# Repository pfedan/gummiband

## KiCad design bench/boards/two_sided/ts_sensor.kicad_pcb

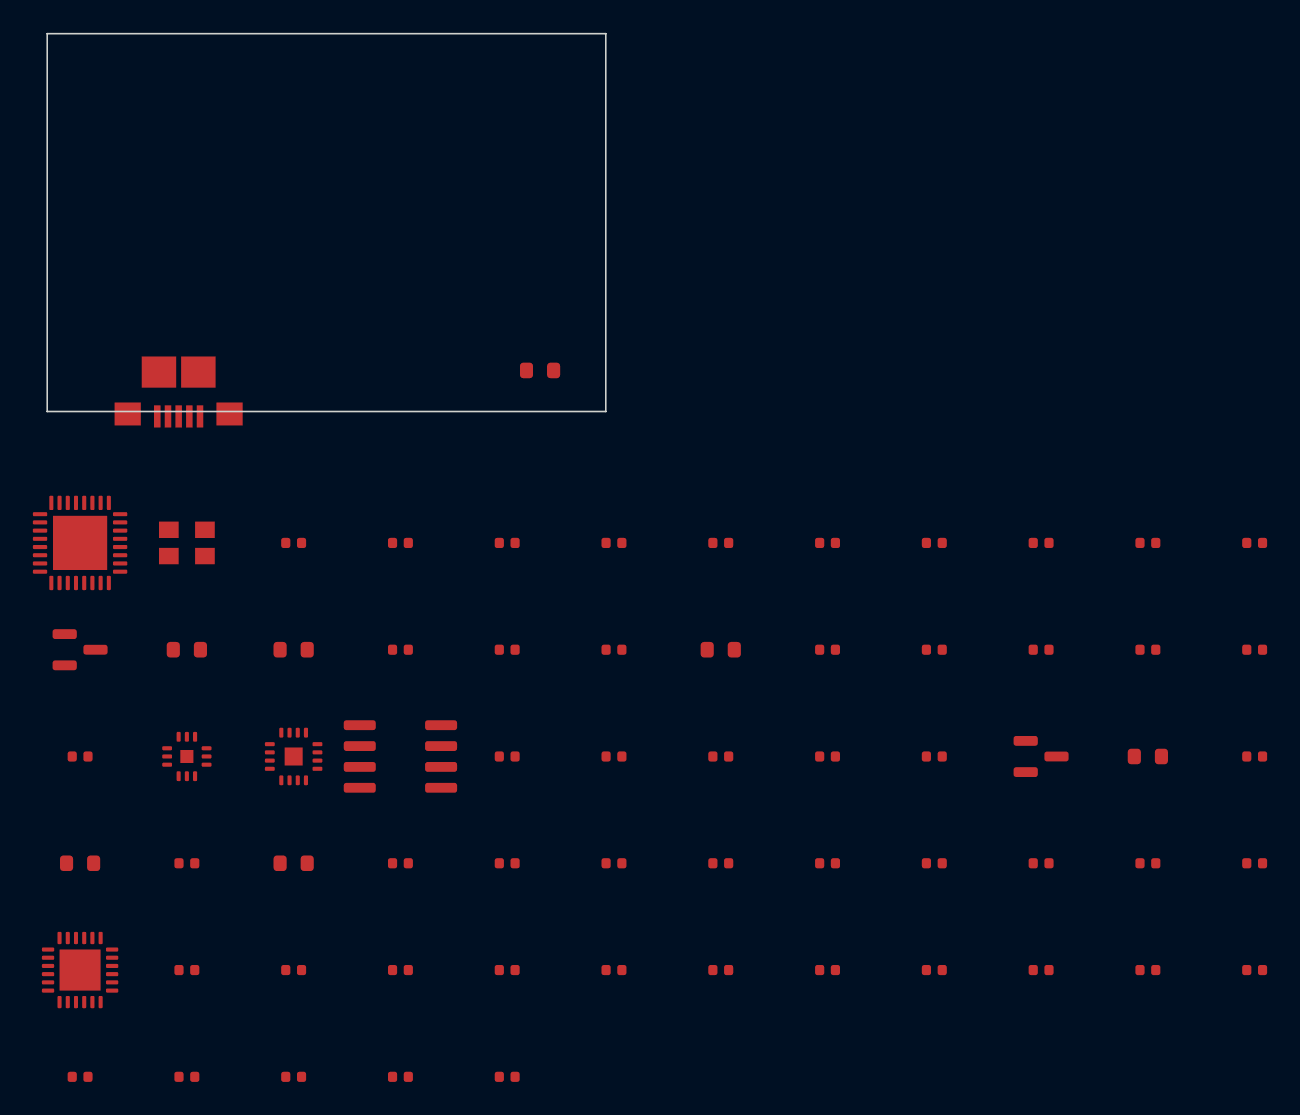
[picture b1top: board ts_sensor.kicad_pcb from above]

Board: 2 copper layers, 34.0 x 23.0 mm, 68 parts (1 on the bottom side), 59 nets, no tracks yet.

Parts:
BT1: CR2032; BatteryHolder_CR2032
C1, C2: 12p; C_0402
C11, C13: 2n2; C_0402
C20, C21, C22, C23: 1p; C_0402
C30, C31, C32, C60, C61, C62, C63, C64, C65, C66, C67, C68, C69: 1u; C_0402
C33: 10u; C_0603
C34, C35, C36, C37, C38, C39, C50, C51, C52: 100n; C_0402
D1, D2: BAT54; D_0603
D10, D11, D12: LED; D_0603
J1: USB; USB_Micro-B_SMD
L10, L12: 2n2; L_0402
R1, R2: 22; R_0402
R10, R11, R12: 1k; R_0402
R20, R21, R22, R23, R24, R25: 10k; R_0402
R30, R31: 1M; R_0402
R40, R41, R42, R43, R44, R45: 47k; R_0402
SW1: BTN; R_0603
U1: Radio; QFN-32
U2: LDO; SOT-23
U3: BME; QFN-12
U4: ACC; QFN-16
U5: Flash; SOIC-8
U6: ESD; SOT-23
U7: EPD; QFN-24
Y1: 32M; Crystal_3225

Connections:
+3V3: C32.1, C33.1, C34.1, C35.1, C36.1, C37.1, C38.1, C39.1, C50.1, C51.1, C52.1, R20.1, R21.1, R22.1, R23.1, R24.1, R25.1, R40.1, R41.1, R42.1, R43.1, R44.1, R45.1, U1.1, U1.9, U1.25, U2.3, U3.1, U4.1, U5.8, U7.1
BTN: SW1.1, U1.29
BUS0: U1.2, U3.2
BUS1: U1.3, U3.3
BUS2: U1.4, U4.2
BUS3: U1.7, U4.3
BUS4: U1.8, U4.4
BUS5: U1.10, U4.5
BUS6: U1.11, U5.1
BUS7: U1.12, U5.2
BUS8: U1.13, U5.3
BUS9: U1.14, U5.5
CP0: C60.1, U7.2
CP1: C61.1, U7.3
CP2: C62.1, U7.4
CP3: C63.1, U7.5
CP4: C64.1, U7.6
CP5: C65.1, U7.7
CP6: C66.1, U7.8
CP7: C67.1, U7.9
CP8: C68.1, U7.10
CP9: C69.1, U7.11
D0: R1.2, U1.15
D1: R2.2, U1.16
DP0: R40.2, U7.15
DP1: R41.2, U7.16
DP2: R42.2, U7.17
DP3: R43.2, U7.18
DP4: R44.2, U7.19
DP5: R45.2, U7.20
GND: BT1.3, C1.2, C2.2, C20.2, C21.2, C22.2, C23.2, C30.2, C31.2, C32.2, C33.2, C34.2, C35.2, C36.2, C37.2, C38.2, C39.2, C50.2, C51.2, C52.2, C60.2, C61.2, C62.2, C63.2, C64.2, C65.2, C66.2, C67.2, C68.2, C69.2, D10.2, D11.2, D12.2, J1.5, J1.S1, J1.S2, J1.S3, J1.S4, R31.2, SW1.2, U1.33, U2.1, U3.13, U4.17, U5.4, U6.3, U7.25, Y1.2, Y1.4
LED0: D10.1, R10.1
LED1: D11.1, R11.1
LED2: D12.1, R12.1
LEDC0: R10.2, U1.18
LEDC1: R11.2, U1.19
LEDC2: R12.2, U1.20
PU0: R20.2, U1.21
PU1: R21.2, U1.22
PU2: R22.2, U1.23
PU3: R23.2, U1.24
PU4: R24.2, U1.26
PU5: R25.2, U1.27
RF0: L10.1, U1.17
RF1: C11.1, C20.1, L10.2
RF2: C11.2, C21.1, L12.1
RF3: C13.1, C22.1, L12.2
RF4: C13.2, C23.1
SPI0: U1.30, U7.12
SPI1: U1.31, U7.13
SPI2: U1.32, U7.14
USB5: J1.2, R1.1, U6.1
USB6: J1.3, R2.1, U6.2
VBAT: BT1.1, BT1.2, D2.1, R30.1
VBUS: D1.1, J1.1
VDIV: R30.2, R31.1, U1.28
VIN: C30.1, C31.1, D1.2, D2.2, U2.2
XI: C1.1, U1.5, Y1.1
XO: C2.1, U1.6, Y1.3

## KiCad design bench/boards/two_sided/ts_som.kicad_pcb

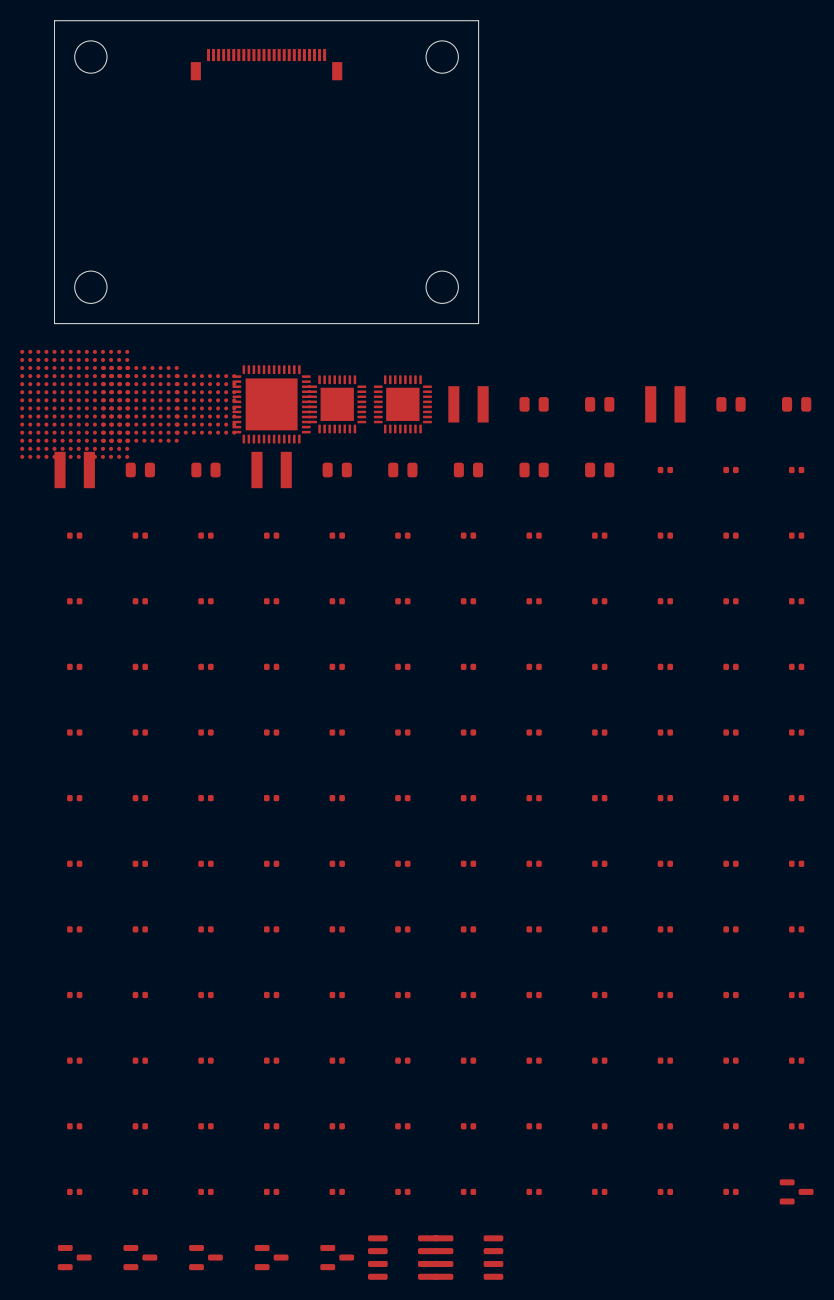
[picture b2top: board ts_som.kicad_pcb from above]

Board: 4 copper layers, 42.0 x 30.0 mm, 169 parts (1 on the bottom side), 158 nets, no tracks yet.

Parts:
C1, C2, C3, C4, C5, C6, C7, C8, C9, C10, C11, C12, C13, C14, C15, C16, C17, C18, C19, C20, C21, C22, C23, C24, C25, C26, C27, C28, C29, C30, C31, C32, C33, C34, C35, C36, C37, C38, C39, C40, C41, C42, C43, C44, C45, C46, C47, C48, C49, C50, C51, C52, C53, C54, C55, C56, C57, C58, C59, C60, C61, C62, C63, C64, C65, C66, C67, C68, C69, C70, C71, C72, C73, C74, C75, C76, C77, C78, C79, C80, C81, C82, C83, C84, C85, C86, C87, C88, C89, C90, C91, C92, C93, C94, C95, C96, C97, C98: 100n; C_0402
C202, C203, C204, C205, C206, C207, C208, C209: 22u; C_0805
C250, C251, C252: 10u; C_0805
H1, H2, H3, H4: MH; MountingHole_3.2mm_M3
J1: B2B; B2B-80
J2: FPC; FPC-24P-0.5mm
L1, L2, L3, L4: 2u2; L_4040
Q1, Q2, Q3, Q4, Q5, Q6: Q; SOT-23
R1, R2, R3, R4, R5, R6, R7, R8, R9, R10, R11, R12, R13, R14, R15, R16, R17, R18, R19, R20, R21, R22, R23, R24, R25, R26, R27, R28, R29, R30, R31, R32, R33, R34, R35, R36: 10k; R_0402
U1: SoC; BGA-196
U2: LPDDR; BGA-100
U3: eMMC; BGA-64
U4: PMIC; QFN-48
U5: PHY; QFN-32
U6: HUB; QFN-32
U7, U8: EEPROM; SOIC-8

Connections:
+1V8: C53.1, C54.1, C55.1, C56.1, C57.1, C58.1, C59.1, C60.1, C61.1, C62.1, C63.1, C64.1, C65.1, C66.1, C67.1, C68.1, C69.1, C70.1, C71.1, C72.1, C73.1, C74.1, C208.1, C209.1, L4.2, R2.2, R3.2, R5.2, R6.2, R8.2, R9.2, R11.2, R12.2, R14.2, R15.2, R17.2, R18.2, R20.2, R21.2, R23.2, R24.2, R26.2, R27.2, R29.2, R30.2, R32.2, R33.2, R35.2, R36.2, U1.B1, U1.C3, U1.D5, U1.E7, U1.F9, U1.G11, U1.H13, U1.K1, U1.L3, U1.M5, U1.N7, U1.P9, U2.A7, U2.B5, U2.C3, U2.D1, U2.D9, U2.E7, U2.F5, U2.G3, U2.H1, U2.H9, U2.J7, U2.K5, U3.A7, U3.B7, U3.C7, U3.D7, U3.E7, U3.F7, U3.G7, U3.H7, U5.11
+3V3: C75.1, C76.1, C77.1, C78.1, C79.1, C80.1, C81.1, C82.1, C83.1, C84.1, C85.1, C86.1, C87.1, C88.1, C89.1, C90.1, C91.1, C92.1, C93.1, C94.1, C95.1, C96.1, C97.1, C98.1, C206.1, C207.1, L3.2, U1.A11, U1.B13, U1.D1, U1.E3, U1.F5, U1.G7, U1.H9, U1.J11, U1.K13, U1.M1, U1.N3, U1.P5, U3.A3, U3.B3, U3.C3, U3.D3, U3.E3, U3.F3, U3.G3, U3.H3, U4.11, U5.4, U6.4, U7.8, U8.8
B2B0: J1.3, U1.A2
B2B1: J1.4, U1.A4
B2B2: J1.5, U1.A8
B2B3: J1.7, U1.A14
B2B4: J1.8, U1.B2
B2B5: J1.10, U1.B4
B2B6: J1.12, U1.B6
B2B7: J1.13, U1.B12
B2B8: J1.14, U1.C8
B2B9: J1.15, U1.D4
B2B10: J1.17, U1.E4
B2B11: J1.18, U1.E8
B2B12: J1.19, U1.E10
B2B13: J1.20, U1.F2
B2B14: J1.22, U1.F6
B2B15: J1.24, U1.F8
B2B16: J1.25, U1.F14
B2B17: J1.27, U1.G4
B2B18: J1.28, U1.G10
B2B19: J1.29, U1.H2
B2B20: J1.32, U5.10
B2B21: J1.33, U5.12
B2B22: J1.34, U5.13
B2B23: J1.35, U5.14
B2B24: J1.38, U5.15
B2B25: J1.39, U5.16
B2B26: J1.40, U6.8
B2B27: J1.42, U6.9
B2B28: J1.43, U6.10
B2B29: J1.45, U6.11
B2B30: J1.47, U6.12
B2B31: J1.48, U6.13
B2B32: J1.49, U6.14
B2B33: J1.50, U6.15
B2B36: J1.54, U4.3
B2B37: J1.55, U4.5
CSI1: J2.2, U1.H10
CSI2: J2.3, U1.J4
CSI3: J2.4, U1.J6
CSI4: J2.5, U1.J8
CSI5: J2.6, U1.J12
CSI7: J2.8, U1.J14
CSI8: J2.9, U1.K6
CSI9: J2.10, U1.K12
CSI10: J2.11, U1.L4
CSI11: J2.12, U1.L6
CSI13: J2.14, U1.M4
CSI14: J2.15, U1.M6
CSI15: J2.16, U1.M10
CSI16: J2.17, U1.M12
CSI17: J2.18, U1.M14
CSI19: J2.20, U1.N4
CSI20: J2.21, U1.N8
CSI21: J2.22, U1.N10
CSI22: J2.23, U1.N12
CSI23: J2.24, U1.P2
DQ0: U1.L10, U2.A2
DQ1: U1.A12, U2.A4
DQ2: U1.B10, U2.A6
DQ3: U1.C4, U2.A8
DQ4: U1.K8, U2.A10
DQ5: U1.K14, U2.B2
DQ6: U1.C2, U2.B4
DQ7: U1.L12, U2.B6
DQ8: U1.M8, U2.B8
DQ9: U1.A10, U2.B10
DQ10: U1.L8, U2.C2
DQ11: U1.H8, U2.C4
DQ12: U1.L2, U2.C6
DQ13: U1.H6, U2.C8
DQ14: U1.E12, U2.C10
DQ15: U1.F12, U2.D2
DQ16: U1.K2, U2.D4
DQ17: U1.H14, U2.D6
DQ18: U1.G2, U2.D8
DQ19: U1.D10, U2.D10
DQ20: U1.K4, U2.E2
DQ21: U1.B8, U2.E4
DQ22: U1.C14, U2.E6
DQ23: U1.H4, U2.E8
DQ24: U1.D2, U2.E10
DQ25: U1.H12, U2.F2
DQ26: U1.G8, U2.F4
DQ27: U1.C6, U2.F6
DQ28: U1.L14, U2.F8
DQ29: U1.G6, U2.F10
EN0: Q1.1, U1.P8
EN1: Q2.1, U1.P14
GND: C1.2, C2.2, C3.2, C4.2, C5.2, C6.2, C7.2, C8.2, C9.2, C10.2, C11.2, C12.2, C13.2, C14.2, C15.2, C16.2, C17.2, C18.2, C19.2, C20.2, C21.2, C22.2, C23.2, C24.2, C25.2, C26.2, C27.2, C28.2, C29.2, C30.2, C31.2, C32.2, C33.2, C34.2, C35.2, C36.2, C37.2, C38.2, C39.2, C40.2, C41.2, C42.2, C43.2, C44.2, C45.2, C46.2, C47.2, C48.2, C49.2, C50.2, C51.2, C52.2, C53.2, C54.2, C55.2, C56.2, C57.2, C58.2, C59.2, C60.2, C61.2, C62.2, C63.2, C64.2, C65.2, C66.2, C67.2, C68.2, C69.2, C70.2, C71.2, C72.2, C73.2, C74.2, C75.2, C76.2, C77.2, C78.2, C79.2, C80.2, C81.2, C82.2, C83.2, C84.2, C85.2, C86.2, C87.2, C88.2, C89.2, C90.2, C91.2, C92.2, C93.2, C94.2, C95.2, C96.2, C97.2, C98.2, C202.2, C203.2, C204.2, C205.2, C206.2, C207.2, C208.2, C209.2, C250.2, C251.2, C252.2, J1.1, J1.6, J1.11, J1.16, J1.21, J1.26, J1.31, J1.36, J1.41, J1.46, J1.51, J1.56, J1.61, J1.66, J1.71, J1.76, J2.1, J2.7, J2.13, J2.19, Q1.2, Q2.2, Q3.2, Q4.2, Q5.2, Q6.2, R1.2, R4.2, R7.2, R10.2, R13.2, R16.2, R19.2, R22.2, R25.2, R28.2, R31.2, R34.2, U1.A1, U1.A5, U1.A9, U1.A13, U1.B3, U1.B7, U1.B11, U1.C1, U1.C5, U1.C9, U1.C13, U1.D3, U1.D7, U1.D11, U1.E1, U1.E5, U1.E9, U1.E13, U1.F3, U1.F7, U1.F11, U1.G1, U1.G5, U1.G9, U1.G13, U1.H3, U1.H7, U1.H11, U1.J1, U1.J5, U1.J9, U1.J13, U1.K3, U1.K7, U1.K11, U1.L1, U1.L5, U1.L9, U1.L13, U1.M3, U1.M7, U1.M11, U1.N1, U1.N5, U1.N9, U1.N13, U1.P3, U1.P7, U1.P11, U2.A1, U2.A5, U2.A9, U2.B3, U2.B7, U2.C1, U2.C5, U2.C9, U2.D3, U2.D7, U2.E1, U2.E5, U2.E9, U2.F3, U2.F7, U2.G1, U2.G5, U2.G9, U2.H3, U2.H7, U2.J1, U2.J5, U2.J9, U2.K3, U2.K7, U3.A1, U3.A5, U3.B1, U3.B5, U3.C1, U3.C5, U3.D1, U3.D5, U3.E1, U3.E5, U3.F1, U3.F5, U3.G1, U3.G5, U3.H1, U3.H5, U4.49, U5.33, U6.33, U7.4, U8.4
MMC0: U1.D12, U3.A2
MMC1: U1.G14, U3.A4
MMC2: U1.N6, U3.A6
MMC3: U1.C10, U3.A8
MMC4: U1.F10, U3.B2
MMC5: U1.E2, U3.B4
MMC6: U1.N14, U3.B6
MMC7: U1.D14, U3.B8
MMC8: U1.J2, U3.C2
MMC9: U1.J10, U3.C4
RGMII0: U1.F4, U5.1
RGMII1: U1.A6, U5.2
RGMII2: U1.D6, U5.3
RGMII3: U1.E14, U5.5
RGMII4: U1.N2, U5.6
RGMII5: U1.P12, U5.7
RGMII6: U1.P10, U5.8
RGMII7: U1.E6, U5.9
STRAP0: R1.1, U6.32
STRAP1: R2.1, U4.35
STRAP2: R3.1, U4.32
STRAP3: R4.1, U4.46
STRAP4: R5.1, U5.25
STRAP5: R6.1, U3.F8
STRAP6: R7.1, U6.19
STRAP7: R8.1, U6.27
STRAP8: R9.1, U3.E2
STRAP9: R10.1, U3.C6
STRAP10: R11.1, U5.23
STRAP11: R12.1, U5.18
STRAP12: R13.1, U5.29
STRAP13: R14.1, U6.29
STRAP14: R15.1, U1.P4
STRAP15: R16.1, U4.10
STRAP16: R17.1, U1.P6
STRAP17: R18.1, U4.18
STRAP18: R19.1, U4.21
STRAP19: R20.1, U5.19
STRAP20: R21.1, U4.33
STRAP21: R22.1, U4.17
STRAP22: R23.1, U4.34
STRAP23: R24.1, U3.E6
STRAP24: R25.1, U4.29
STRAP25: R26.1, U6.22
STRAP26: R27.1, U4.23
STRAP27: R28.1, U3.G8
STRAP28: R29.1, U4.31
STRAP29: R30.1, U3.H2
STRAP30: R31.1, U3.F6
STRAP31: R32.1, U6.25
STRAP32: R33.1, U5.20
STRAP33: R34.1, U4.20
STRAP34: R35.1, U3.E4
STRAP35: R36.1, U6.20
SW_1V8: L4.1, U4.37, U4.38
SW_3V3: L3.1, U4.25, U4.26
SW_VDD_CORE: L1.1, U4.1, U4.2
SW_VDD_DDR: L2.1, U4.13, U4.14
ULPI0: U1.M2, U6.1
ULPI1: U1.G12, U6.2
ULPI2: U1.D8, U6.3
ULPI3: U1.C12, U6.5
ULPI4: U1.K10, U6.6
ULPI5: U1.B14, U6.7
VDD_CORE: C1.1, C2.1, C3.1, C4.1, C5.1, C6.1, C7.1, C8.1, C9.1, C10.1, C11.1, C12.1, C13.1, C14.1, C15.1, C16.1, C17.1, C18.1, C19.1, C20.1, C21.1, C22.1, C23.1, C24.1, C25.1, C26.1, C27.1, C28.1, C29.1, C30.1, C202.1, C203.1, L1.2, U1.A3, U1.B5, U1.C7, U1.D9, U1.E11, U1.F13, U1.H1, U1.J3, U1.K5, U1.L7, U1.M9, U1.N11, U1.P13
VDD_DDR: C31.1, C32.1, C33.1, C34.1, C35.1, C36.1, C37.1, C38.1, C39.1, C40.1, C41.1, C42.1, C43.1, C44.1, C45.1, C46.1, C47.1, C48.1, C49.1, C50.1, C51.1, C52.1, C204.1, C205.1, L2.2, U1.A7, U1.B9, U1.C11, U1.D13, U1.F1, U1.G3, U1.H5, U1.J7, U1.K9, U1.L11, U1.M13, U1.P1, U2.A3, U2.B1, U2.B9, U2.C7, U2.D5, U2.E3, U2.F1, U2.F9, U2.G7, U2.H5, U2.J3, U2.K1, U2.K9
VIN: C250.1, C251.1, C252.1, J1.2, J1.9, J1.23, J1.30, J1.37, J1.44, J1.58, J1.65, J1.72, J1.79, U4.4

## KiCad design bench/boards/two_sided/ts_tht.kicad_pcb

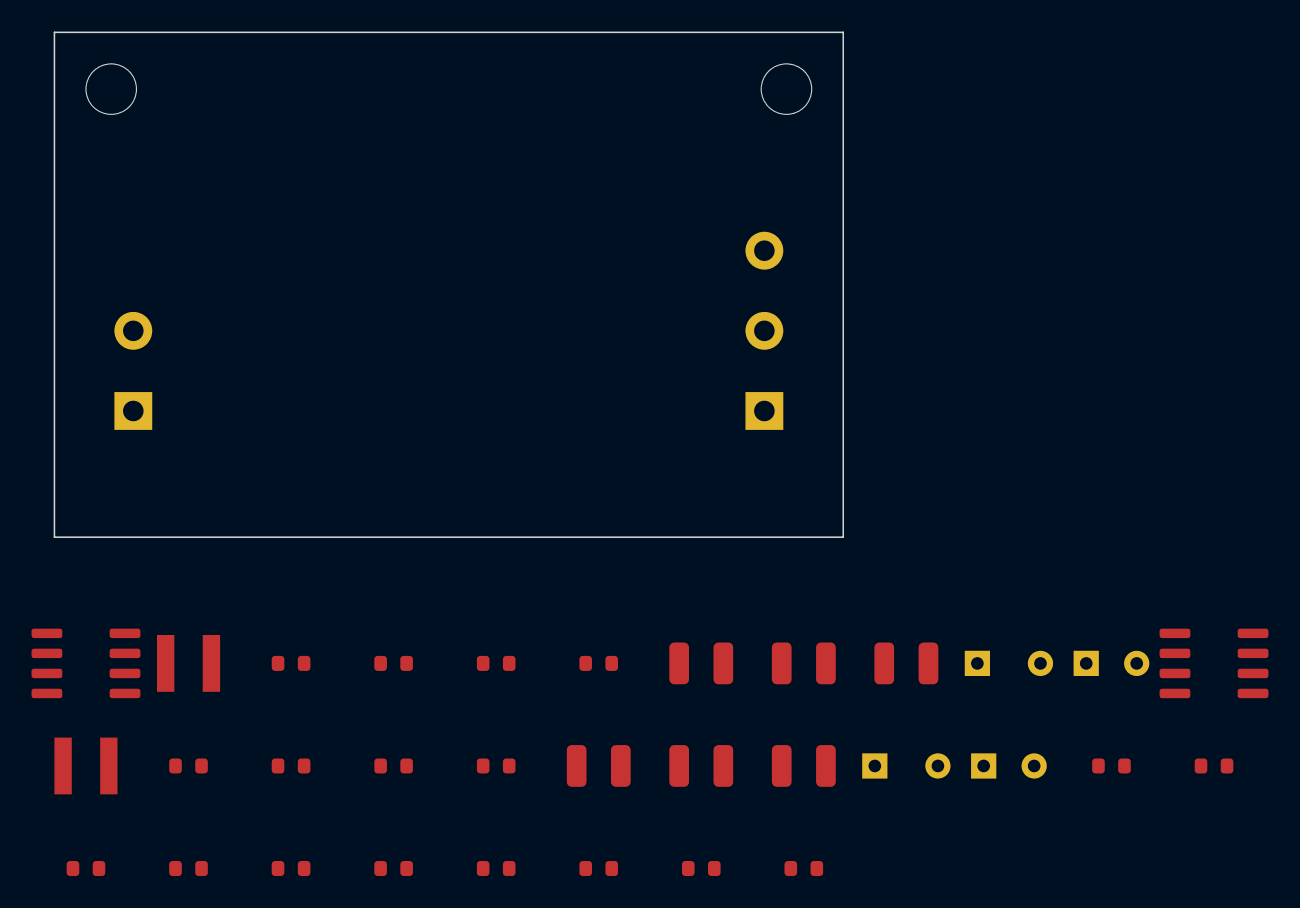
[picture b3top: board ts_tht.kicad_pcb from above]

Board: 2 copper layers, 50.0 x 32.0 mm, 36 parts (0 on the bottom side), 12 nets, no tracks yet.

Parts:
C10, C20, C40, C41, C42, C43, C44, C45, C46, C47, C48, C49: 100n; C_0603
C11, C12, C13, C21, C22, C23: 22u; C_1210
C15, C25: 220u; CP_Radial_D10mm
C16, C26: 220u; CP_Radial_D8mm
H1, H2: MH; MountingHole_3.2mm_M3
J1: Term; TerminalBlock_1x02_P5.08mm
J2: Term; TerminalBlock_1x03_P5.08mm
L1, L2: 10u; L_4040
R10, R11, R20, R21: 10k; R_0603
R15, R25: 100k; R_0603
U1, U2: BUCK; SOIC-8

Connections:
+5V: C12.1, C13.1, C16.1, C40.1, C45.1, C46.1, C47.1, J2.1, L1.2, R10.1
+12V: C22.1, C23.1, C26.1, C42.1, C49.1, J2.2, L2.2, R20.1
BST1: C10.1, U1.3
BST2: C20.1, U2.3
EN1: R15.2, U1.6
EN2: R25.2, U2.6
FB1: R10.2, R11.1, U1.5
FB2: R20.2, R21.1, U2.5
GND: C11.2, C12.2, C13.2, C15.2, C16.2, C21.2, C22.2, C23.2, C25.2, C26.2, C40.2, C41.2, C42.2, C43.2, C44.2, C45.2, C46.2, C47.2, C48.2, C49.2, J1.2, J2.3, R11.2, R21.2, U1.4, U2.4
SW1: C10.2, L1.1, U1.2, U1.8
SW2: C20.2, L2.1, U2.2, U2.8
VIN: C11.1, C15.1, C21.1, C25.1, C41.1, C43.1, C44.1, C48.1, J1.1, R15.1, R25.1, U1.1, U2.1
